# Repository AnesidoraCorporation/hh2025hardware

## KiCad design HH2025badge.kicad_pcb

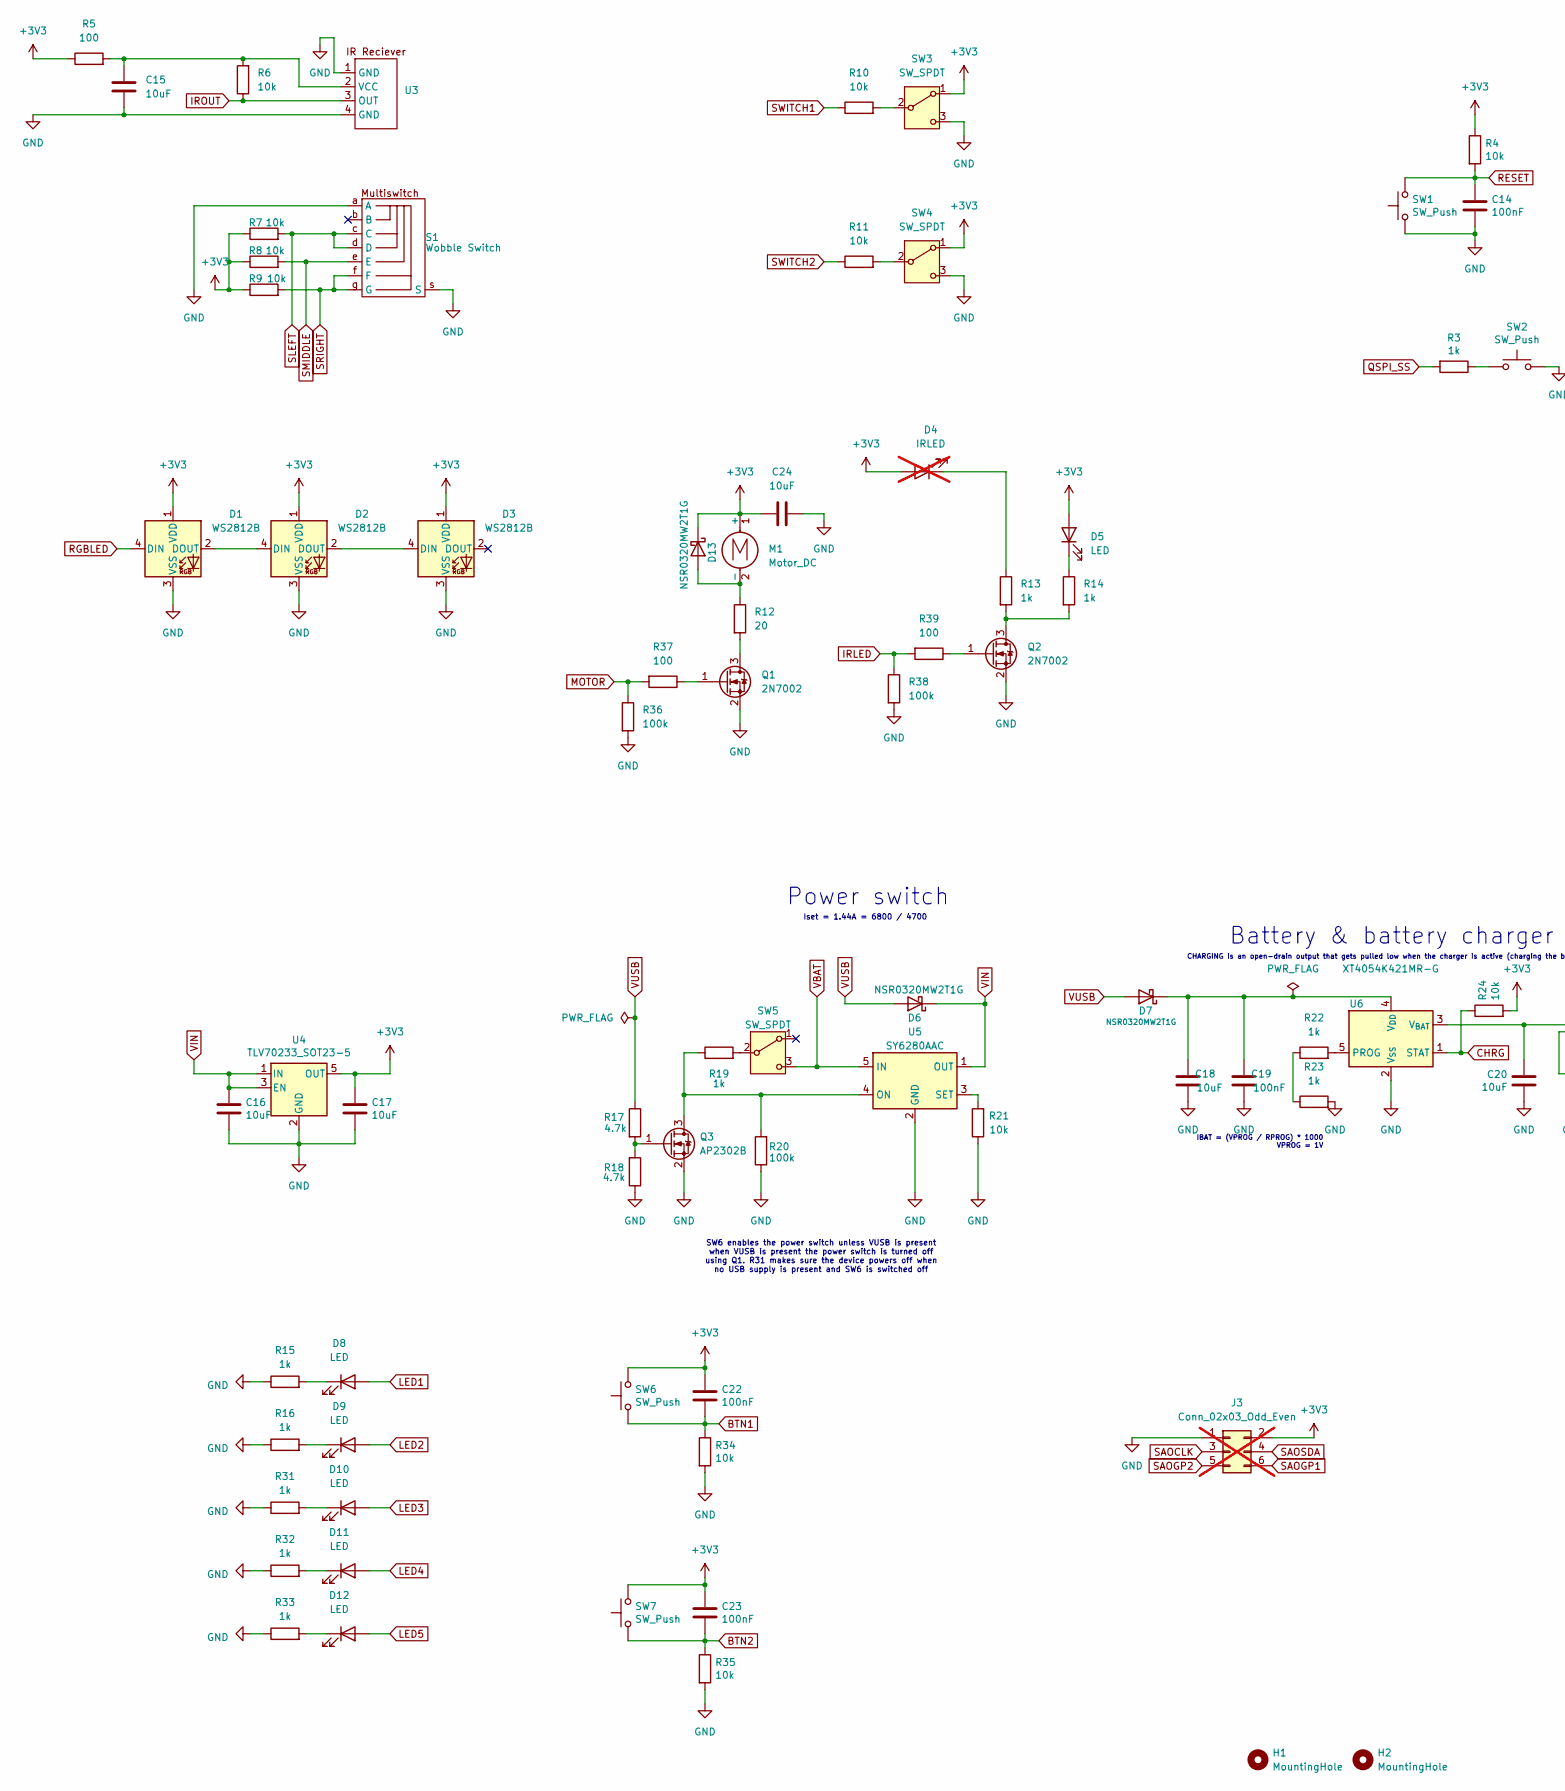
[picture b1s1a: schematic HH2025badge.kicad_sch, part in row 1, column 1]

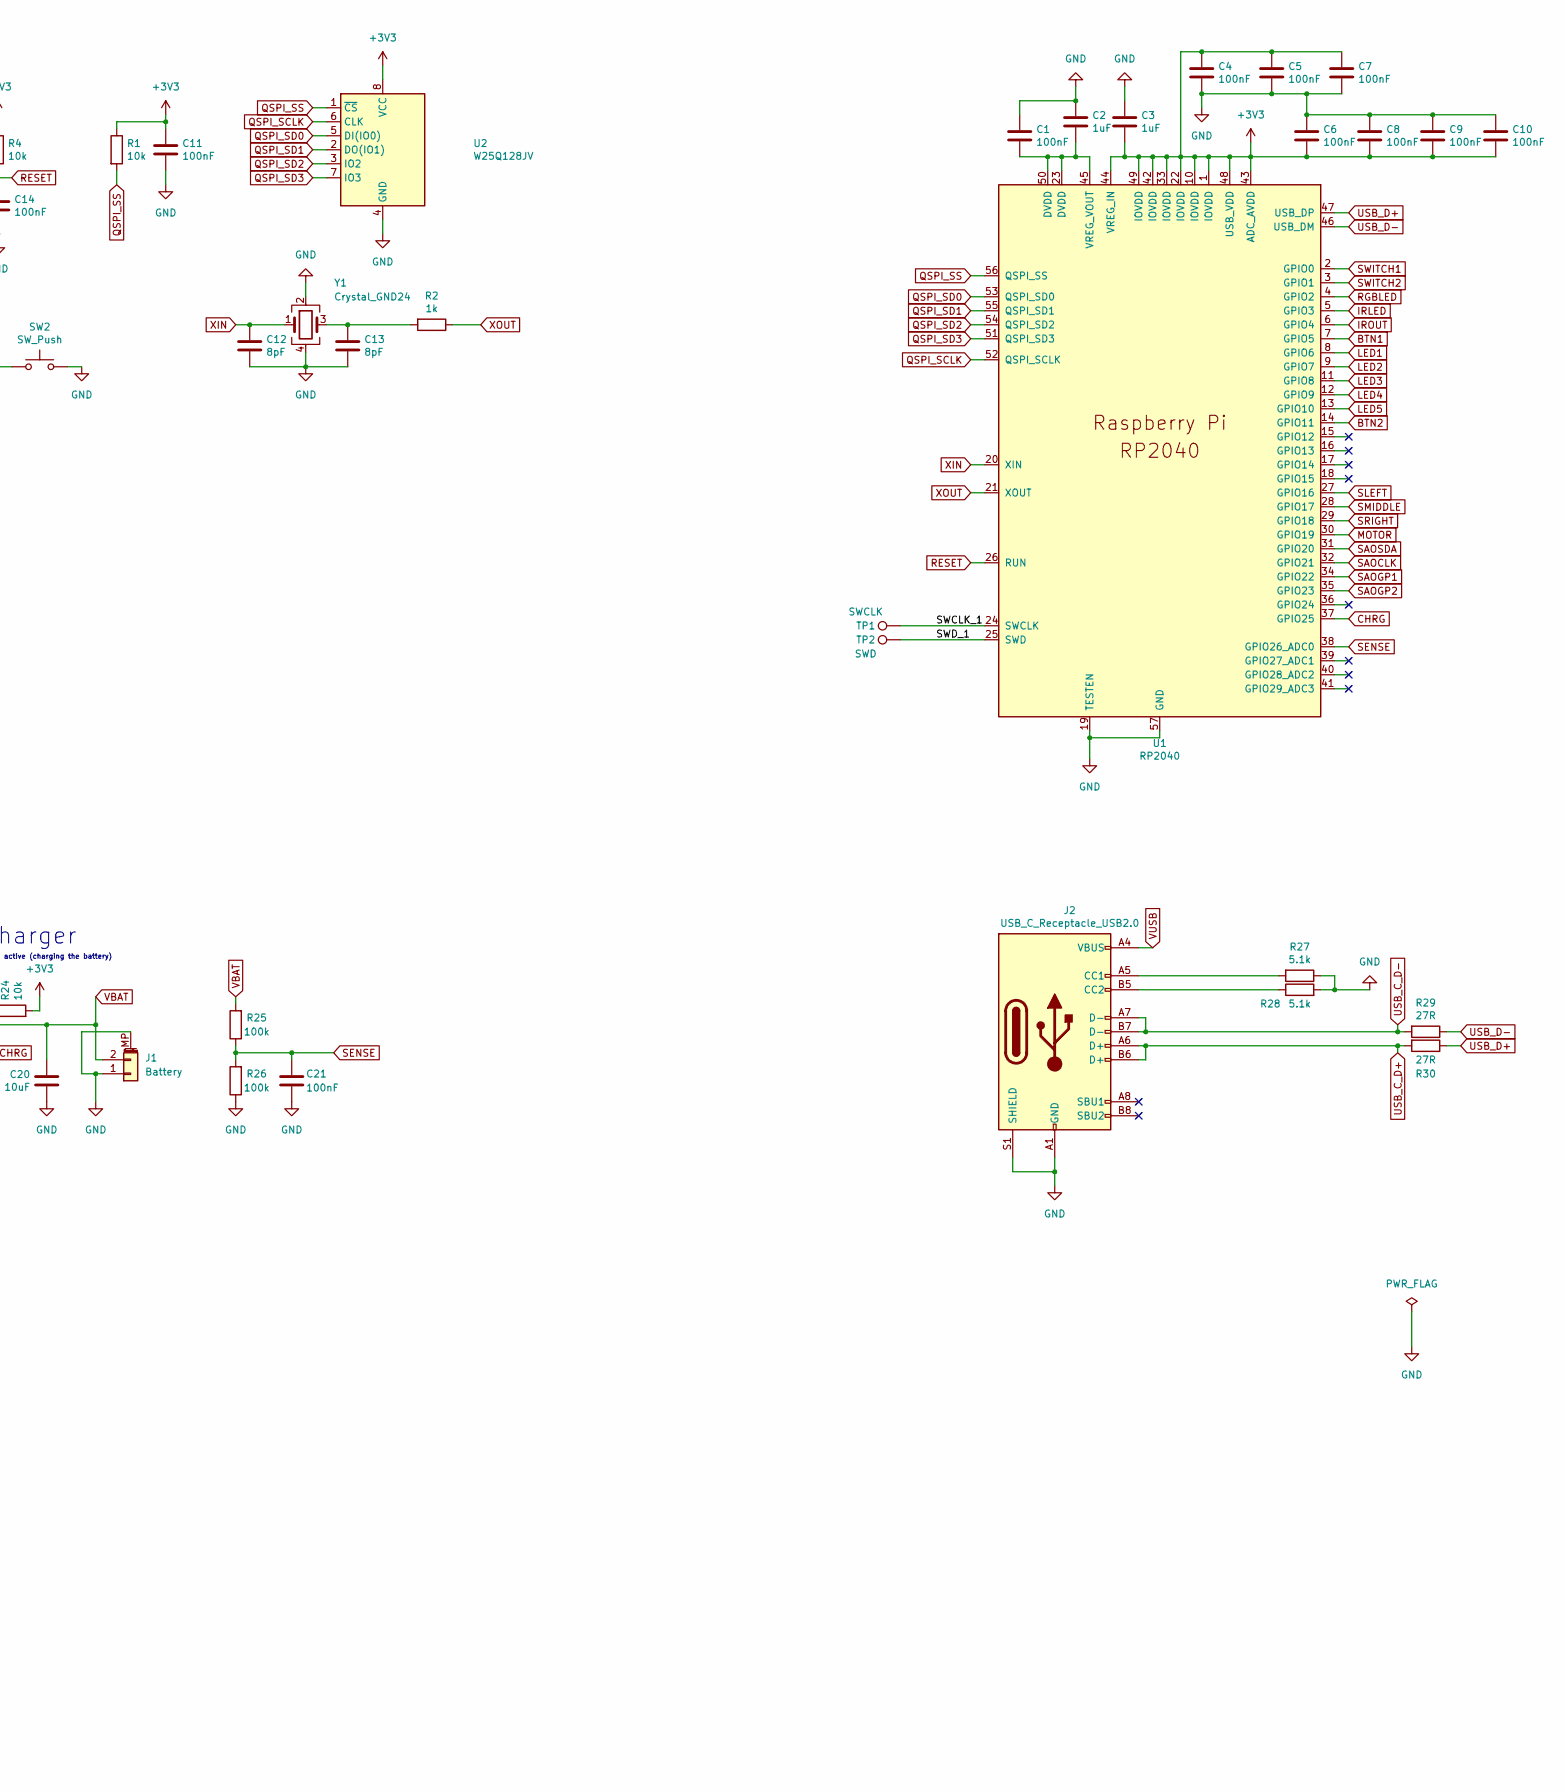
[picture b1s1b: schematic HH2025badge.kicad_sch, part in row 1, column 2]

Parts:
C1, C4, C5, C6, C7, C8, C9, C10, C11, C14, C19, C21, C22, C23: 100nF; C_0402_1005Metric; LCSC C1525
C2, C3: 1uF; C_0402_1005Metric; LCSC C52923
C12, C13: 8pF; C_0402_1005Metric; LCSC C296006
C15, C16, C17, C18, C20, C24: 10uF; C_0805_2012Metric; LCSC C89189
D1, D2, D3: WS2812B; LED_WS2812B_PLCC4_5.0x5.0mm_P3.2mm; LCSC C4154882
D4: IRLED; LED_D5.0mm_IRGrey; LCSC DNP; not fitted
D5, D8, D9, D10, D11, D12: LED; LED_0603_1608Metric; LCSC C72038
D6, D7, D13: NSR0320MW2T1G; D_SOD-323; LCSC C48192
H1, H2: MountingHole; MountingHole_3.2mm_M3; LCSC DNP
J1: Battery; JST_S2B-ZR-SM4A-TF(LF)(SN); LCSC C2681533
J2: USB_C_Receptacle_USB2.0; USB_C_Receptacle_HRO_TYPE-C-31-M-12; LCSC C167321
J3: Conn_02x03_Odd_Even; PinHeader_2x03_P2.54mm_Vertical; LCSC DNP; not fitted
M1: Motor_DC; PinHeader_1x02_P2.54mm_Vertical; LCSC DNP
Q1, Q2: 2N7002; SOT-23; LCSC C389059
Q3: AP2302B; SOT-23; LCSC C406812
R1, R4, R6, R7, R8, R9, R10, R11, R21, R24, R34, R35: 10k; R_0402_1005Metric; LCSC C25744
R2, R3, R13, R14, R15, R16, R19, R22, R23, R31, R32, R33: 1k; R_0402_1005Metric; LCSC C11702
R5, R37, R39: 100; R_0805_2012Metric; LCSC C17408
R12: 20; R_0805_2012Metric; LCSC C212359
R17, R18: 4.7k; R_0805_2012Metric; LCSC C2907326
R20, R25, R26, R36, R38: 100k; R_0402_1005Metric; LCSC C25741
R27, R28: 5.1k; R_0402_1005Metric; LCSC C25905
R29, R30: 27R; R_0402_1005Metric; LCSC C25100
S1: Wobble Switch; SW-SMD_TM-1011A; LCSC C318960
SW1, SW2, SW6, SW7: SW_Push; SW_SPST_TL3305A; LCSC C92581
SW3, SW4, SW5: SW_SPDT; SW_SPDT_PCM12; LCSC C319020
TP1: SWCLK; TestPoint_Pad_D1.0mm; LCSC DNP
TP2: SWD; TestPoint_Pad_D1.0mm; LCSC DNP
U1: RP2040; RP2040-QFN-56; LCSC C2040
U2: W25Q128JV; SOIC-8_5.23x5.23mm_P1.27mm; LCSC C97521
U3: OPTO-SMD_IRM-V838M3-C-TR1; LCSC C3291489
U4: TLV70233_SOT23-5; SOT-23-5; LCSC C118233
U5: SY6280AAC; SOT-23-5; LCSC C55136
U6: XT4054K421MR-G; SOT-23-5; LCSC C141405
Y1: Crystal_GND24; Crystal_SMD_3225-4Pin_3.2x2.5mm; LCSC C255902

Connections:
+3V3: C3.2, C4.1, C5.1, C6.2, C7.1, C8.2, C9.2, C10.2, C11.1, C17.1, C22.1, C23.1, C24.1, D1.1 (VDD), D2.1 (VDD), D3.1 (VDD), D4.2 (A), D5.2 (A), D13.1 (K), J3.2, M1.1 (+), R1.1, R4.1, R5.1, R7.1, R8.1, R9.1, R24.2, SW3.1 (A), SW4.1 (A), SW6.2, SW7.2, U1.1 (IOVDD), U1.10 (IOVDD), U1.22 (IOVDD), U1.33 (IOVDD), U1.42 (IOVDD), U1.43 (ADC_AVDD), U1.44 (VREG_IN), U1.48 (USB_VDD), U1.49 (IOVDD), U2.8 (VCC), U4.5 (OUT)
/SWCLK_1: TP1.1, U1.24 (SWCLK)
/SWD_1: TP2.1, U1.25 (SWD)
BTN1: C22.2, R34.1, SW6.1, U1.7 (GPIO5)
BTN2: C23.2, R35.1, SW7.1, U1.14 (GPIO11)
CHRG: R24.1, U1.37 (GPIO25), U6.1 (STAT)
GND: C1.1, C2.1, C3.1, C4.2, C5.2, C6.1, C7.2, C8.1, C9.1, C10.1, C11.2, C12.2, C13.2, C14.2, C15.2, C16.2, C17.2, C18.1, C19.1, C20.2, C21.2, C24.2, D1.3 (VSS), D2.3 (VSS), D3.3 (VSS), J1.1, J1.MP (MountPin), J2.A1 (GND), J2.A12 (GND), J2.B1 (GND), J2.B12 (GND), J2.S1 (SHIELD), J3.1, Q1.2 (S), Q2.2 (S), Q3.2 (S), R15.1, R16.1, R18.1, R20.1, R21.1, R23.2, R26.1, R27.1, R28.2, R31.1, R32.1, R33.1, R34.2, R35.2, R36.2, R38.2, S1.a (A), S1.s (S), SW1.1, SW2.2, SW3.3 (C), SW4.3 (C), U1.19 (TESTEN), U1.57 (GND), U2.4 (GND), U3.1 (GND), U3.4 (GND), U4.2 (GND), U5.2 (GND), U6.2 (V_{SS}), Y1.2, Y1.4
IRLED: R38.1, R39.2, U1.5 (GPIO3)
IROUT: R6.1, U1.6 (GPIO4), U3.3 (OUT)
LED1: D8.2 (A), U1.8 (GPIO6)
LED2: D9.2 (A), U1.9 (GPIO7)
LED3: D10.2 (A), U1.11 (GPIO8)
LED4: D11.2 (A), U1.12 (GPIO9)
LED5: D12.2 (A), U1.13 (GPIO10)
MOTOR: R36.1, R37.2, U1.30 (GPIO19)
unnamed: C13.1, R2.2, Y1.3
unnamed: D1.2 (DOUT), D2.4 (DIN)
unnamed: D2.2 (DOUT), D3.4 (DIN)
unnamed: D4.1 (K), R13.1
unnamed: D5.1 (K), R14.1
unnamed: C18.2, C19.2, D7.1 (K), U6.4 (V_{DD})
unnamed: D8.1 (K), R15.2
unnamed: D9.1 (K), R16.2
unnamed: D10.1 (K), R31.2
unnamed: D11.1 (K), R32.2
unnamed: D12.1 (K), R33.2
unnamed: D13.2 (A), M1.2 (-), R12.1
unnamed: J2.A5 (CC1), R27.2
unnamed: J2.B5 (CC2), R28.1
unnamed: Q1.3 (D), R12.2
unnamed: Q1.1 (G), R37.1
unnamed: Q2.3 (D), R13.2, R14.2
unnamed: Q2.1 (G), R39.1
unnamed: Q3.3 (D), R19.1, R20.2, U5.4 (ON)
unnamed: Q3.1 (G), R17.2, R18.2
unnamed: R3.1, SW2.1
unnamed: R22.1, R23.1
unnamed: R10.2, SW3.2 (B)
unnamed: R11.2, SW4.2 (B)
unnamed: R19.2, SW5.2 (B)
unnamed: C1.2, C2.2, U1.23 (DVDD), U1.45 (VREG_VOUT), U1.50 (DVDD)
unnamed: C15.1, R5.2, R6.2, U3.2 (VCC)
unnamed: R21.2, U5.3 (SET)
unnamed: R22.2, U6.5 (PROG)
QSPI_SCLK: U1.52 (QSPI_SCLK), U2.6 (CLK)
QSPI_SD0: U1.53 (QSPI_SD0), U2.5 (DI(IO0))
QSPI_SD1: U1.55 (QSPI_SD1), U2.2 (DO(IO1))
QSPI_SD2: U1.54 (QSPI_SD2), U2.3 (IO2)
QSPI_SD3: U1.51 (QSPI_SD3), U2.7 (IO3)
QSPI_SS: R1.2, R3.2, U1.56 (QSPI_SS), U2.1 (~CS)
RESET: C14.1, R4.2, SW1.2, U1.26 (RUN)
RGBLED: D1.4 (DIN), U1.4 (GPIO2)
SAOCLK: J3.3, U1.32 (GPIO21)
SAOGP1: J3.6, U1.34 (GPIO22)
SAOGP2: J3.5, U1.35 (GPIO23)
SAOSDA: J3.4, U1.31 (GPIO20)
SENSE: C21.1, R25.1, R26.2, U1.38 (GPIO26_ADC0)
SLEFT: R7.2, S1.c (C), S1.d (D), U1.27 (GPIO16)
SMIDDLE: R8.2, S1.e (E), U1.28 (GPIO17)
SRIGHT: R9.2, S1.f (F), S1.g (G), U1.29 (GPIO18)
SWITCH1: R10.1, U1.2 (GPIO0)
SWITCH2: R11.1, U1.3 (GPIO1)
USB_C_D+: J2.A6 (D+), J2.B6 (D+), R30.2
USB_C_D-: J2.A7 (D-), J2.B7 (D-), R29.2
USB_D+: R30.1, U1.47 (USB_DP)
USB_D-: R29.1, U1.46 (USB_DM)
VBAT: C20.1, J1.2, R25.2, SW5.3 (C), U5.5 (IN), U6.3 (V_{BAT})
VIN: C16.1, D6.1 (K), U4.1 (IN), U4.3 (EN), U5.1 (OUT)
VUSB: D6.2 (A), D7.2 (A), J2.A4 (VBUS), J2.A9 (VBUS), J2.B4 (VBUS), J2.B9 (VBUS), R17.1
XIN: C12.1, U1.20 (XIN), Y1.1
XOUT: R2.1, U1.21 (XOUT)

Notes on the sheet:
Iset = 1.44A = 6800 / 4700
IBAT = (VPROG / RPROG) * 1000 VPROG = 1V
Battery & battery charger
Power switch
SW6 enables the power switch unless VUSB is present when VUSB is present the power switch is turned off using Q1. R31 makes sure the device powers off when no USB supply is present and SW6 is switched off
CHARGING is an open-drain output that gets pulled low when the charger is active (charging the battery)

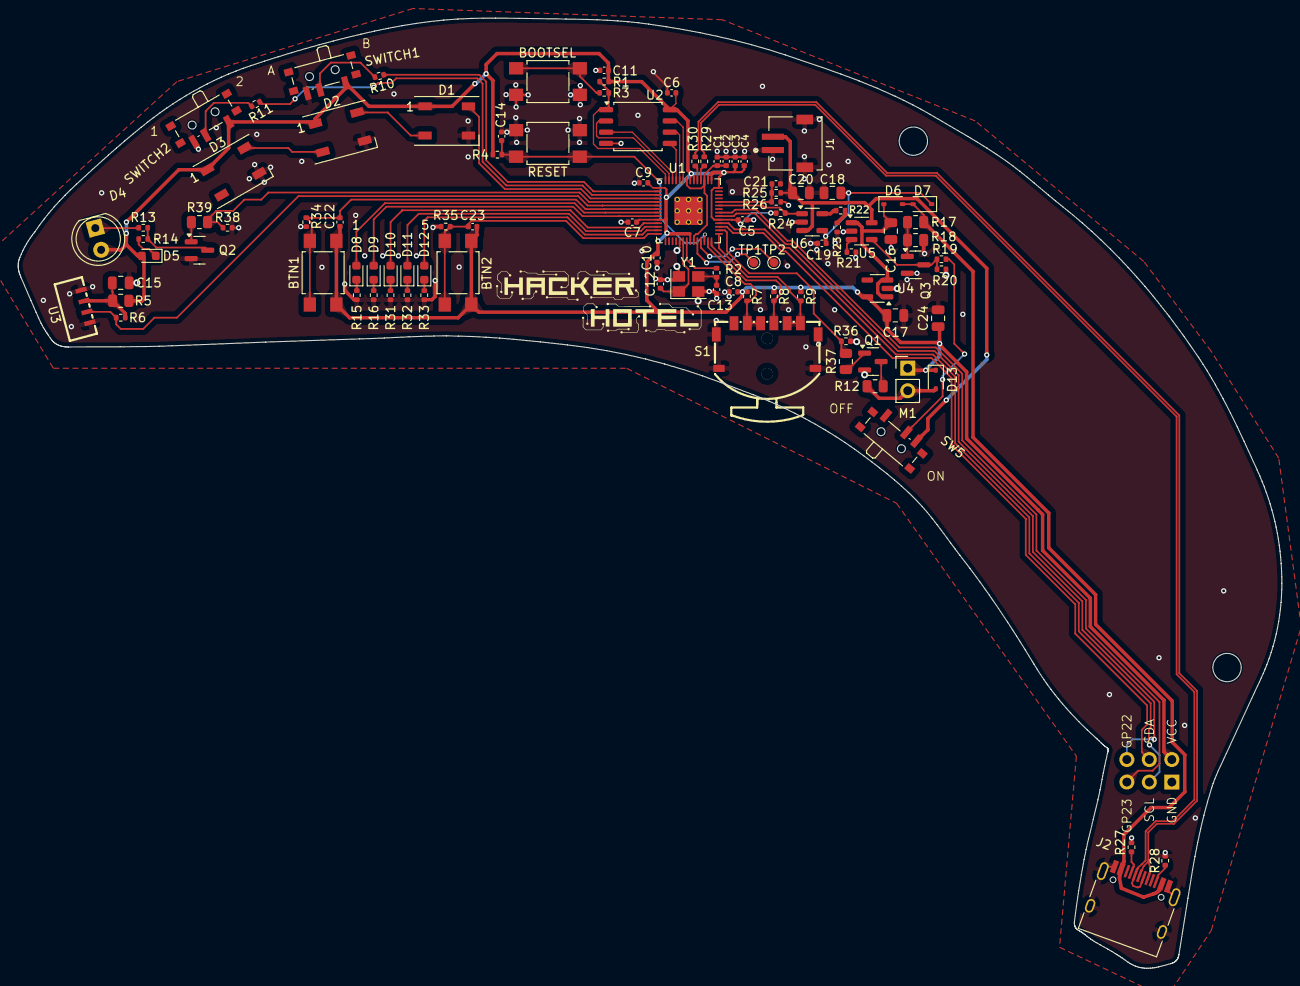
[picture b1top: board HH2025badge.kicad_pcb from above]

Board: 2 copper layers, 142.7 x 107.3 mm, 102 parts (1 on the bottom side), 71 nets.

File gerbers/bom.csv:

Designator,Footprint,Quantity,Value,LCSC Part #
"C1, C10, C11, C14, C19, C21, C22, C23, C4, C5, C6, C7, C8, C9",0402,14,100nF,C1525
"C12, C13",0402,2,8pF, C296006
"C15, C16, C17, C18, C20, C24",0805,6,10uF,C89189
"C2, C3",0402,2,1uF,C52923
"D1, D2, D3",LED_WS2812B_PLCC4_5.0x5.0mm_P3.2mm,3,WS2812B,C4154882
"D10, D11, D12, D5, D8, D9",0603,6,LED,C72038
"D13, D6, D7",D_SOD-323,3,NSR0320MW2T1G,C48192
D4,LED_D5.0mm_IRGrey,1,IRLED,DNP
J1,JST_S2B-ZR-SM4A-TF(LF)(SN),1,Battery,C2681533
J2,USB_C_Receptacle_HRO_TYPE-C-31-M-12,1,USB_C_Receptacle_USB2.0,C167321
J3,PinHeader_2x03_P2.54mm_Vertical,1,Conn_02x03_Odd_Even,DNP
M1,PinHeader_1x02_P2.54mm_Vertical,1,Motor_DC,DNP
"Q1, Q2",SOT-23,2,2N7002,C389059
Q3,SOT-23,1,AP2302B,C406812
"R1, R10, R11, R21, R24, R34, R35, R4, R6, R7, R8, R9",0402,12,10k,C25744
R12,0805,1,20,C212359
"R13, R14, R15, R16, R19, R2, R22, R23, R3, R31, R32, R33",0402,12,1k,C11702
"R17, R18",0805,2,4.7k,C2907326
"R20, R25, R26, R36, R38",0402,5,100k,C25741
"R27, R28",0402,2,5.1k,C25905
"R29, R30",0402,2,27R,C25100
"R37, R39, R5",0805,3,100, C17408
S1,SW-SMD_TM-1011A,1,Wobble Switch,C318960
"SW1, SW2, SW6, SW7",SW_SPST_TL3305A,4,SW_Push,C92581
"SW3, SW4, SW5",SW_SPDT_PCM12,3,SW_SPDT,C319020
TP1,TestPoint_Pad_D1.0mm,1,SWCLK,DNP
TP2,TestPoint_Pad_D1.0mm,1,SWD,DNP
U1,RP2040-QFN-56,1,RP2040,C2040
U2,SOIC-8_5.23x5.23mm_P1.27mm,1,W25Q128JV,C97521
U3,OPTO-SMD_IRM-V838M3-C-TR1,1,~,C3291489
U4,SOT-23-5,1,TLV70233_SOT23-5,C118233
U5,SOT-23-5,1,SY6280AAC,C55136
U6,SOT-23-5,1,XT4054K421MR-G,C141405
Y1,Crystal_SMD_3225-4Pin_3.2x2.5mm,1,Crystal_GND24,C255902

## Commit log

2025-02-13 Uploaded schematic
2025-02-14 Added all production files
